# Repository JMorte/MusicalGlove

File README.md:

# MusicalGlove

The directories are structured by this way:

Arduino folder contains the Processing code of the Transmitter and the receiver.
Design folder includes the Hardware design, the schematic and board with its corresponding images.
Video folder have two demonstrations of the features of the glove.

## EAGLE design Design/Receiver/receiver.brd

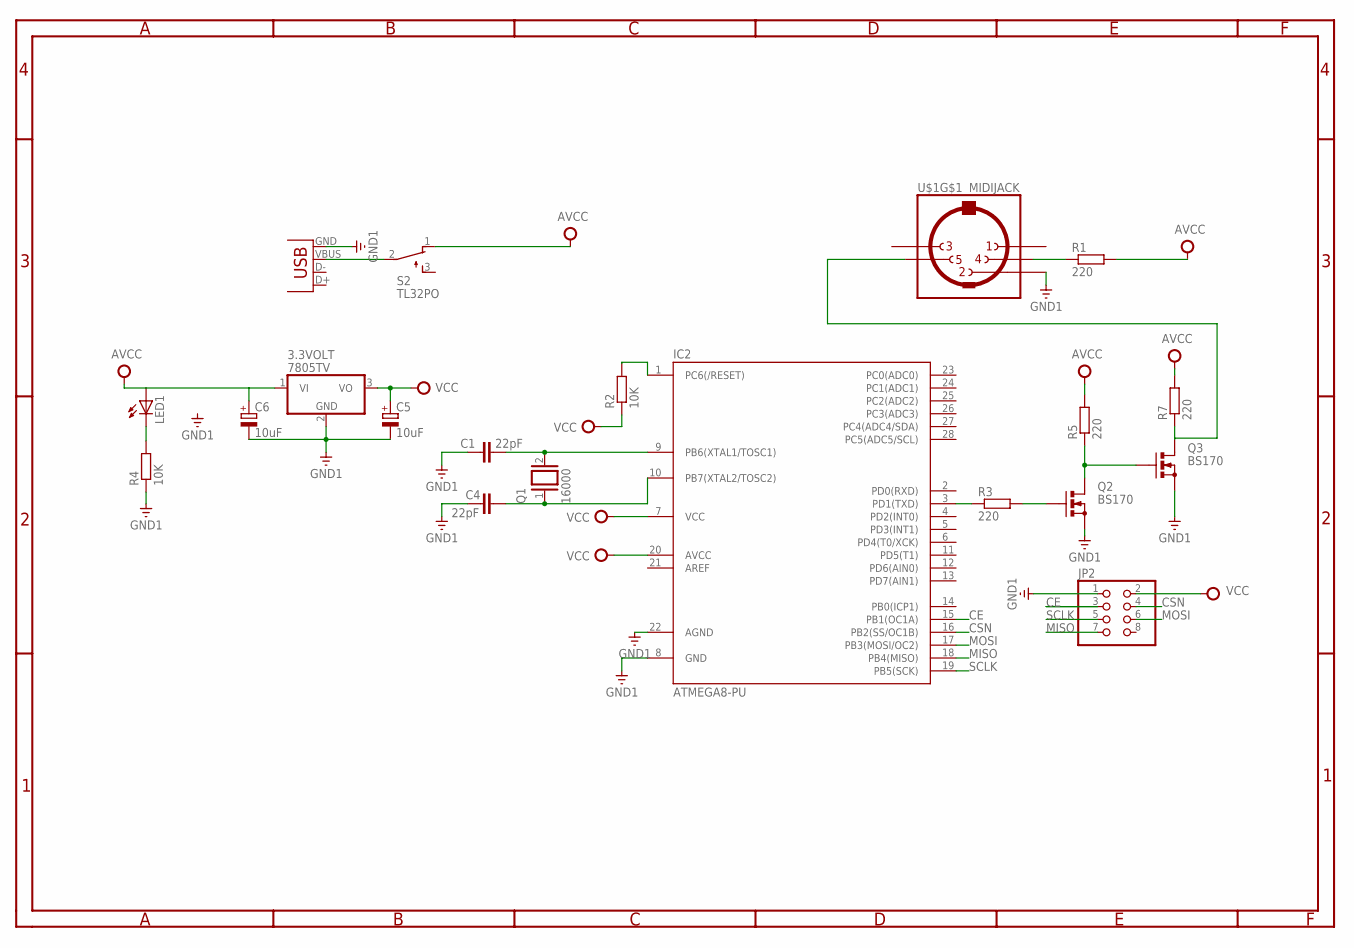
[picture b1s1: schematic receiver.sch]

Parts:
3.3VOLT: 7805TV; TO220V
C1, C4: 22pF; C050-025X075
C5, C6: 10uF; E2,5-5
IC2: ATMEGA8-PU; DIL28-3
JP2: PINHD-2X4; 2X04
LED1: LED5MM
Q1: 16000; QS
Q2, Q3: BS170; SOT54E
R1, R3, R5, R7: 220; 0204/7
R2, R4: 10K; 0204/7
S2: TL32PO; TL3XPO
U$1: MIDIJACK; CP-2350
X1: USB-B-H

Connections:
AVCC: 3.3VOLT.1 (VI), C6.+, LED1.A, R1.2, R5.2, R7.2, S2.1 (O)
CE: IC2.15 (PB1(OC1A)), JP2.3
CSN: IC2.16 (PB2(SS/OC1B)), JP2.4
GND1: 3.3VOLT.2 (GND), C1.1, C4.1, C5.-, C6.-, IC2.8 (GND), IC2.22 (AGND), JP2.1, Q2.S, Q3.S, R4.1, U$1.2, X1.GND
MISO: IC2.18 (PB4(MISO)), JP2.7
MOSI: IC2.17 (PB3(MOSI/OC2)), JP2.6
unnamed: C1.2, IC2.9 (PB6(XTAL1/TOSC1)), Q1.2
unnamed: C4.2, IC2.10 (PB7(XTAL2/TOSC2)), Q1.1
unnamed: S2.2, X1.VBUS
unnamed: LED1.K (C), R4.2
unnamed: IC2.3 (PD1(TXD)), R3.1
unnamed: Q2.G, R3.2
unnamed: IC2.1 (PC6(/RESET)), R2.2
unnamed: Q2.D, Q3.G, R5.1
unnamed: R1.1, U$1.4
unnamed: Q3.D, R7.1, U$1.5
SCLK: IC2.19 (PB5(SCK)), JP2.5
VCC: 3.3VOLT.3 (VO), C5.+, IC2.7 (VCC), IC2.20 (AVCC), JP2.2, R2.1

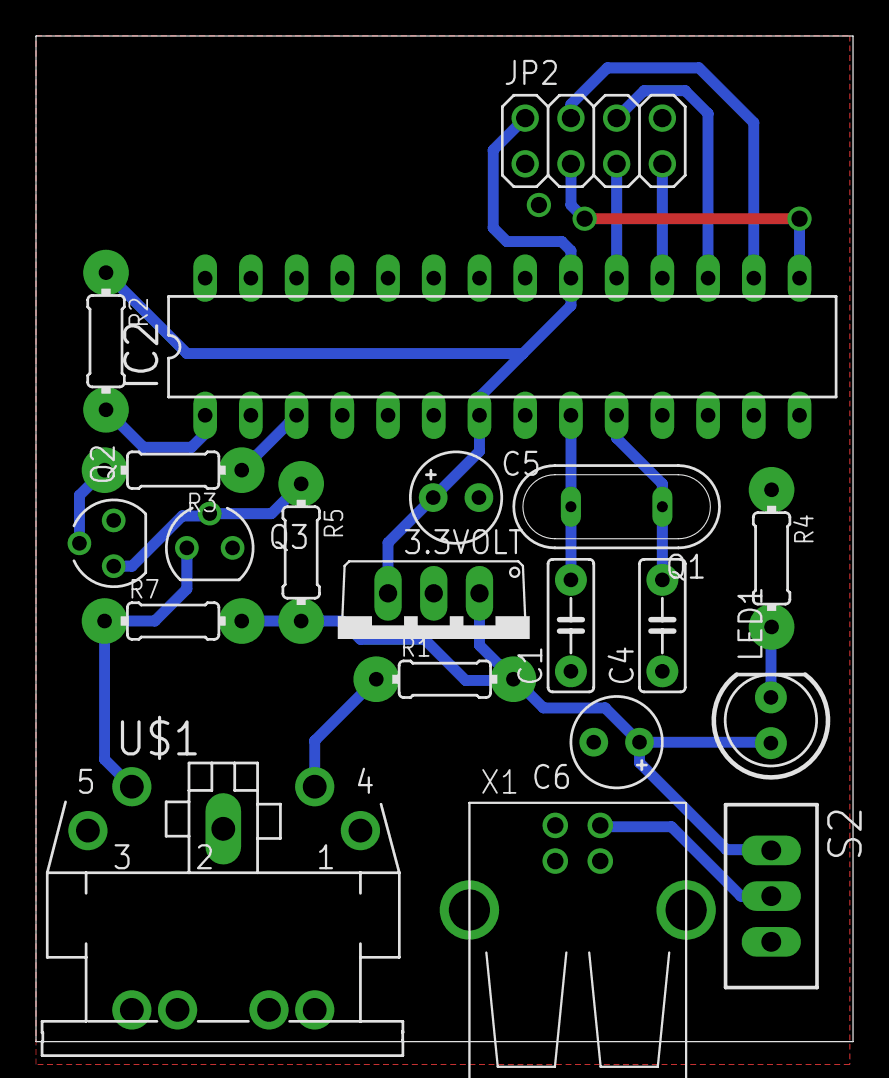
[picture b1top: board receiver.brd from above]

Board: 2 copper layers, 45.4 x 55.9 mm, 20 parts (0 on the bottom side), 18 nets.

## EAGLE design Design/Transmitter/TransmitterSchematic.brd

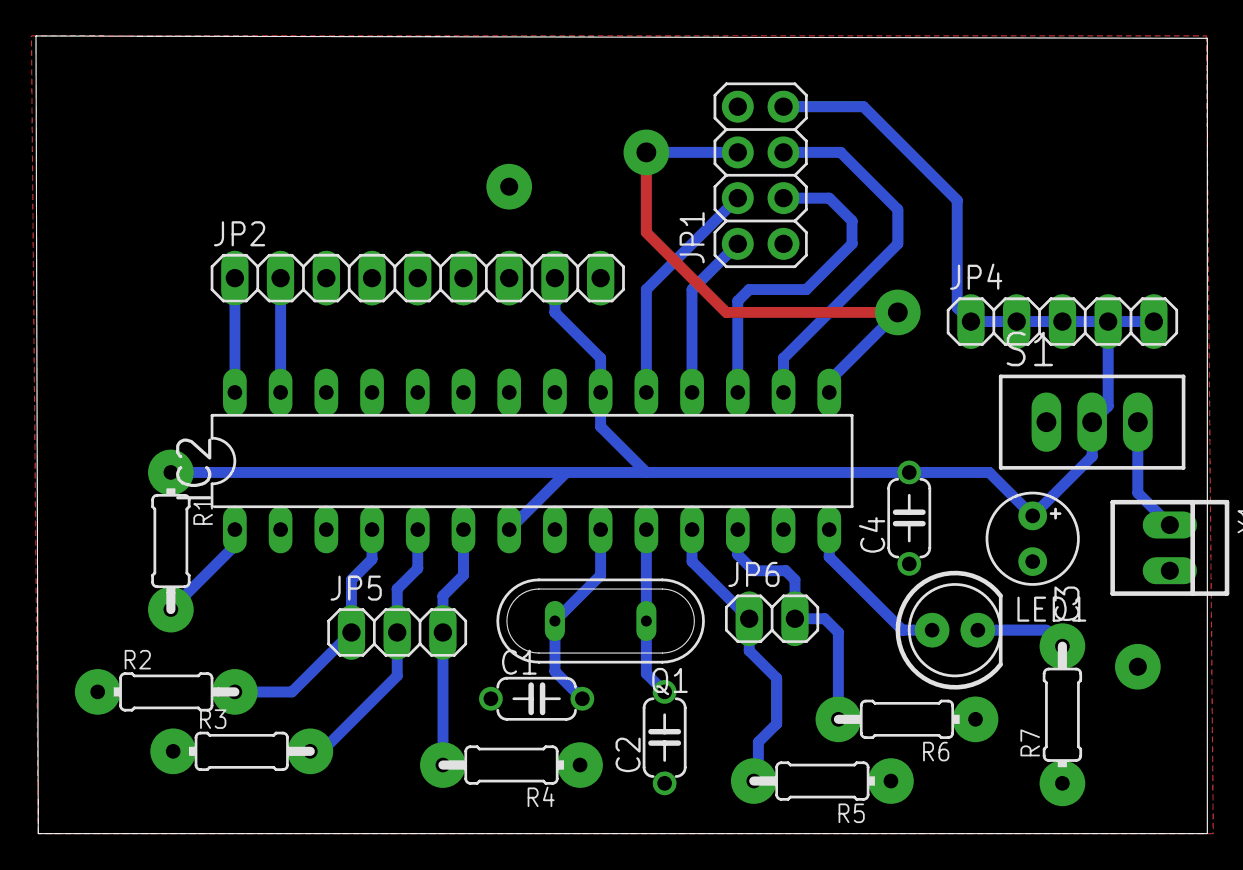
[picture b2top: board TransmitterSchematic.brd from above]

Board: 2 copper layers, 65.1 x 44.3 mm, 21 parts (0 on the bottom side), 20 nets.

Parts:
C1, C2: 22pF; C050-024X044
C3: 10uF; E2,5-5
C4: 1nF; C050-024X044
IC2: ATMEGA328-20P; DIL28-3
JP1: 2X04
JP2: 1X09
JP4: 1X05
JP5: 1X03
JP6: 1X02
LED1: LED5MM
Q1: QS
R1, R2, R3, R4, R5, R6: 10k; 0204/7
R7: 220; 0204/7
S1: TL32PO; TL3XPO
X1: 22-23-2021

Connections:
CE: IC2.15, JP1.6
CSN: IC2.16, JP1.5
D2: IC2.4, JP5.1, R2.2
D3: IC2.5, JP5.2, R3.2
D4: IC2.6, JP5.3, R4.2
D5: IC2.11, JP6.1, R5.2
D6: IC2.12, JP6.2, R6.2
GND: C1.1, C2.1, C3.-, C4.1, IC2.8, IC2.22, JP1.8, JP2.7, R2.1, R3.1, R4.1, R5.1, R6.1, R7.1, X1.2
LED: IC2.14, LED1.A
MISO: IC2.18, JP1.2
MOSI: IC2.17, JP1.3
unnamed: C1.2, IC2.9, Q1.2
unnamed: C2.2, IC2.10, Q1.1
unnamed: IC2.1, R1.2
unnamed: LED1.K, R7.2
unnamed: S1.3, X1.1
SCK: IC2.19, JP1.4
SCL: IC2.28, JP2.1
SDA: IC2.27, JP2.2
VCC: C3.+, C4.2, IC2.7, IC2.20, JP1.7, JP2.8, JP4.1, JP4.2, JP4.3, JP4.4, JP4.5, R1.1, S1.2

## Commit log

2016-06-21 second commit
2016-06-22 prueba subiendo
2016-06-22 Last update

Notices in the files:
parts and their libraries:
dframes: Copyright (C) 2004, Bob Starr (bobstarr@mindspring.com)
